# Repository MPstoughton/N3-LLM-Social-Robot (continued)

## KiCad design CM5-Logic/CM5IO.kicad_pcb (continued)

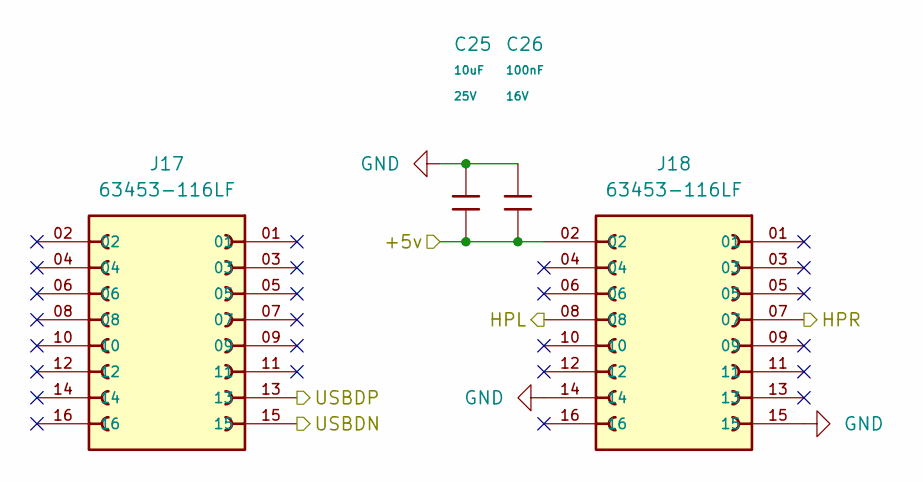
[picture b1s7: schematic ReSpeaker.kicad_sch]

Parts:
C25: 10uF; C_0805; Voltage Rated 25V; Tolerance ±10%; Part CL21A106KAYNNNE; LCSC C15850
C26: 100nF; C_0402; Voltage Rated 16V; Tolerance ±10%; Part CL05B104KO5NNNC; LCSC C1525
J17, J18: 63453-116LF; AMPHENOL_63453-116LF

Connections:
/+5v: C25.2, C26.2, J18.02; also elsewhere on the board
/HPL: J18.08; also elsewhere on the board
/HPR: J18.07; also elsewhere on the board
/USB2-D_N: J17.15; also elsewhere on the board
/USB2-D_P: J17.13; also elsewhere on the board
GND: C25.1, C26.1, J18.14, J18.15; also elsewhere on the board

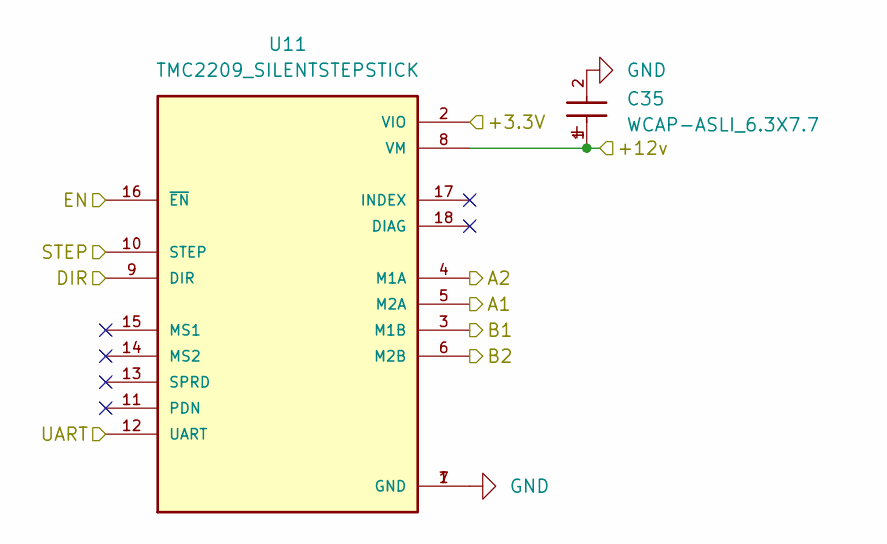
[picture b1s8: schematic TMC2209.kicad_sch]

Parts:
C35: WCAP-ASLI_6.3X7.7; WCAP-ASLI_6.3X7.7_DXL_
U11: TMC2209_SILENTSTEPSTICK; MODULE_TMC2209_SILENTSTEPSTICK; PARTREV 1.20

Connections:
/+3.3v_ESP32: U11.2 (VIO); also elsewhere on the board
/+12v: C35.1, U11.8 (VM); also elsewhere on the board
/TMC2209/A1: U11.5 (M2A); also elsewhere on the board
/TMC2209/A2: U11.4 (M1A); also elsewhere on the board
/TMC2209/B1: U11.3 (M1B); also elsewhere on the board
/TMC2209/B2: U11.6 (M2B); also elsewhere on the board
/n_Dir: U11.9 (DIR); also elsewhere on the board
/n_EN: U11.16 (~EN); also elsewhere on the board
/n_Step: U11.10 (STEP); also elsewhere on the board
/n_UART: U11.12 (UART); also elsewhere on the board
GND: C35.2, U11.1 (GND), U11.7 (GND); also elsewhere on the board

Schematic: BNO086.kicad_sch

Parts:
J13, J14: 6130XX11821_61300811821; 61300811821

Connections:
/+3.3v_ESP32: J13.4, J14.2; also elsewhere on the board
/BNO086/CS: J14.6
/BNO086/SCK: J14.3
/BNO086/SI: J14.5
/BNO086/SO: J14.4
/BNO086/WAK: J14.7
/n_INT: J13.8; also elsewhere on the board
/n_RST: J13.7; also elsewhere on the board
/n_SenseSCL: J13.6; also elsewhere on the board
/n_SenseSDA: J13.5; also elsewhere on the board
GND: J13.1, J13.2, J13.3, J14.1; also elsewhere on the board

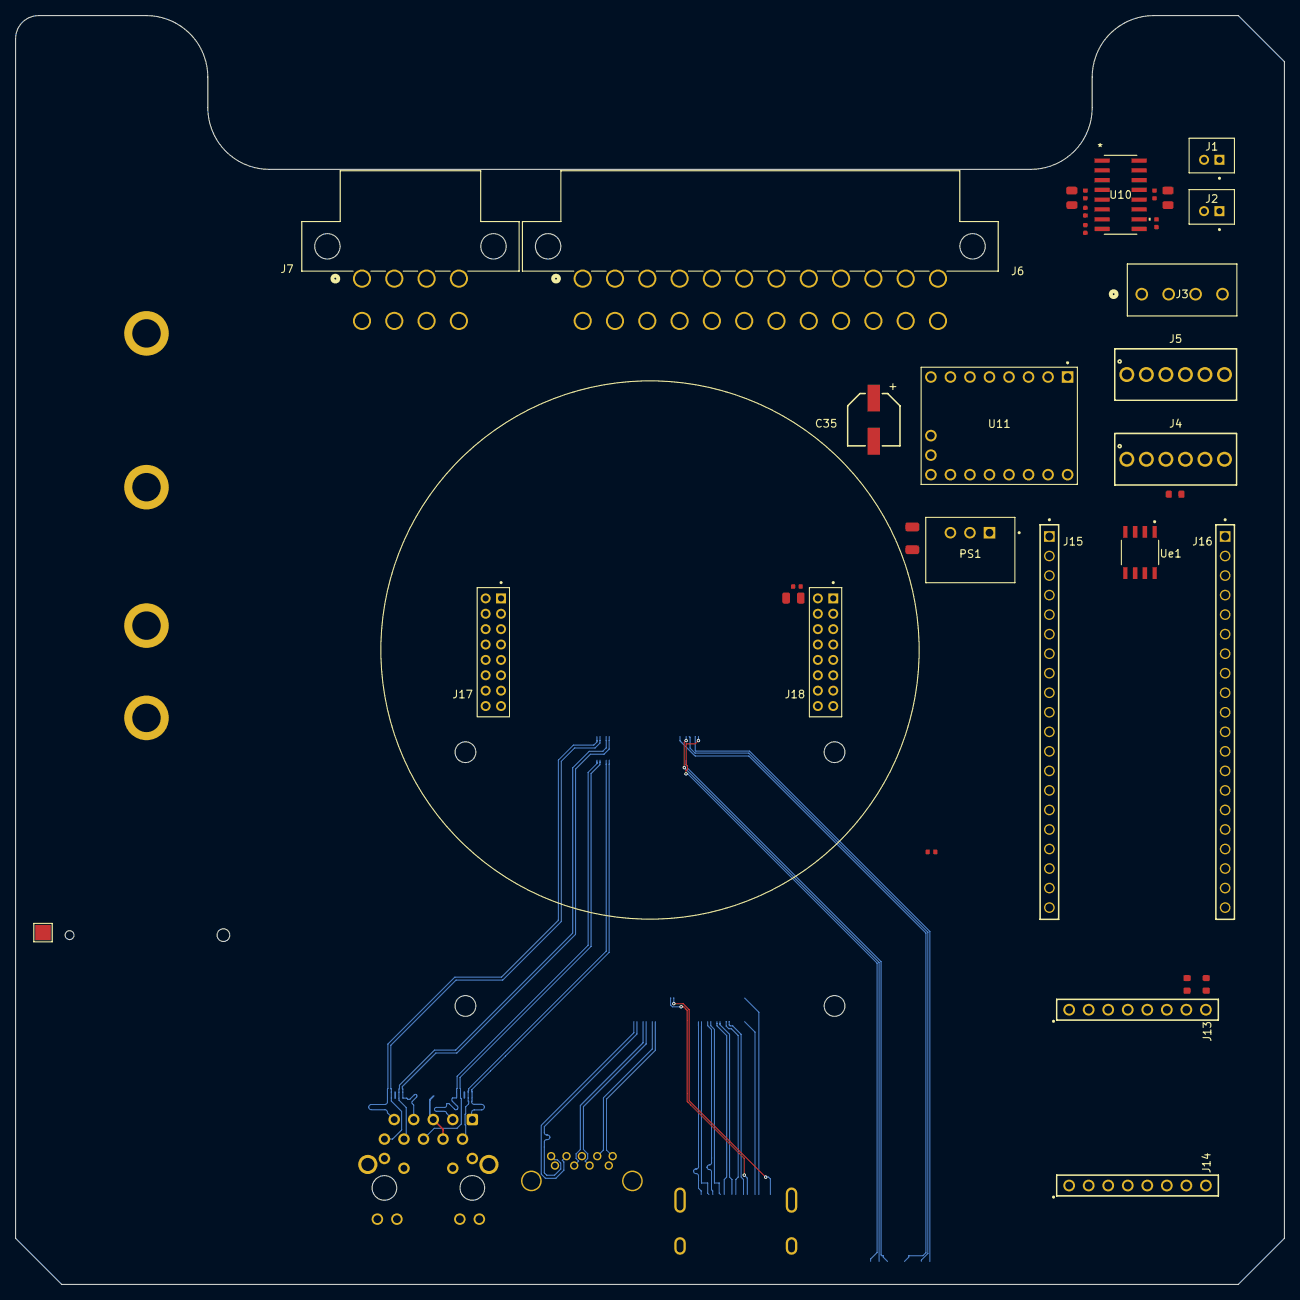
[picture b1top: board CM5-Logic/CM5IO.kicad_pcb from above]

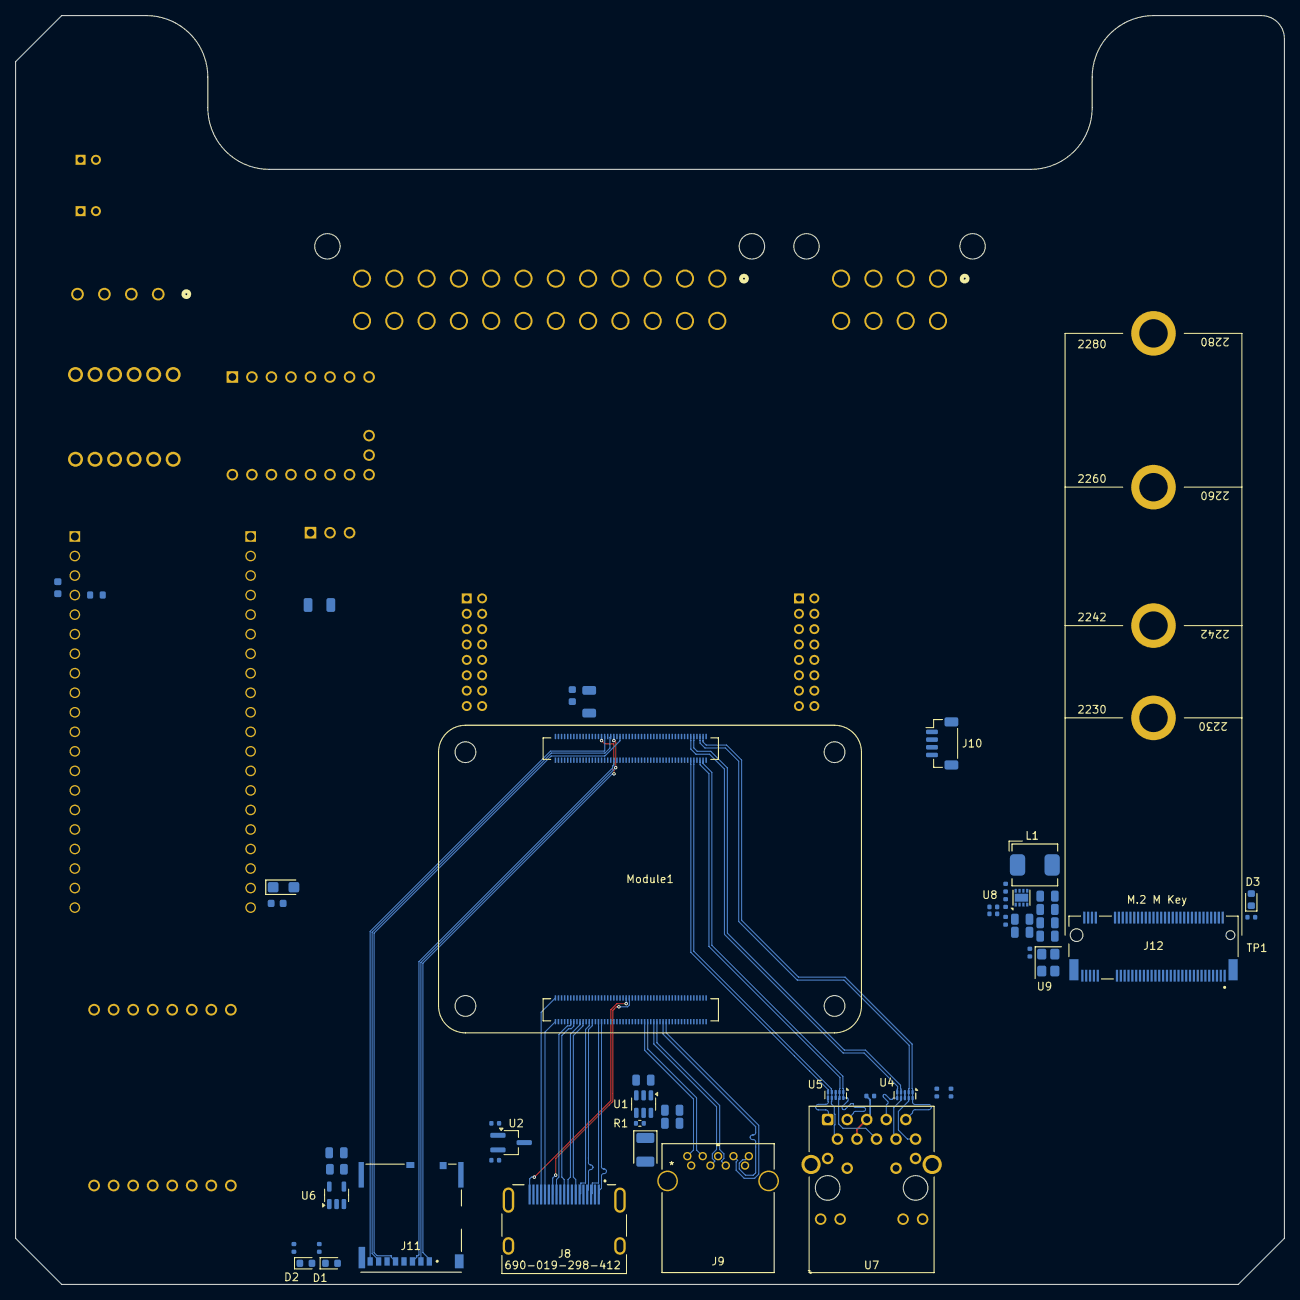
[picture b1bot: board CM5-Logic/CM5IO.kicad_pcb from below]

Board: 4 copper layers, 165.0 x 165.0 mm, 85 parts (52 on the bottom side), 107 nets.

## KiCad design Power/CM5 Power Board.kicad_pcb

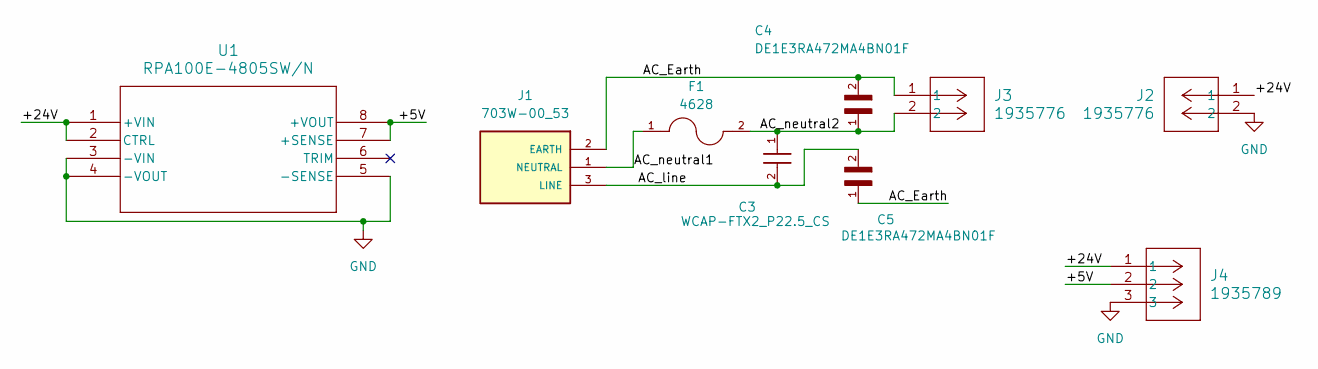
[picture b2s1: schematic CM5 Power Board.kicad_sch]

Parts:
C3: WCAP-FTX2_P22.5_CS; WCAP-FTX2_P22.5L26W6H12_CS
C4, C5: DE1E3RA472MA4BN01F; CAP_DE1E3RA472MA4BN01F
F1: 4628; FUSE_4628
J1: 703W-00_53; QUALTEK_703W-00_53
J2, J3: 1935776; CONN_1935776_PXC
J4: 1935789; CONN_1935789_PXC
U1: RPA100E-4805SW/N; RPA100E-W_RCP

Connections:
/+5V: J4.2, U1.7 (+SENSE), U1.8 (+VOUT)
/+24V: J2.1, J4.1, U1.1 (+VIN), U1.2 (CTRL)
/AC_Earth: C4.2, C5.1, J1.2 (EARTH), J3.1
/AC_line: C3.2, C5.2, J1.3 (LINE)
/AC_neutral1: F1.1, J1.1 (NEUTRAL)
/AC_neutral2: C3.1, C4.1, F1.2, J3.2
GND: J2.2, J4.3, U1.3 (-VIN), U1.4 (-VOUT), U1.5 (-SENSE)

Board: 2 copper layers, 9 parts (0 on the bottom side), 7 nets, no tracks yet.

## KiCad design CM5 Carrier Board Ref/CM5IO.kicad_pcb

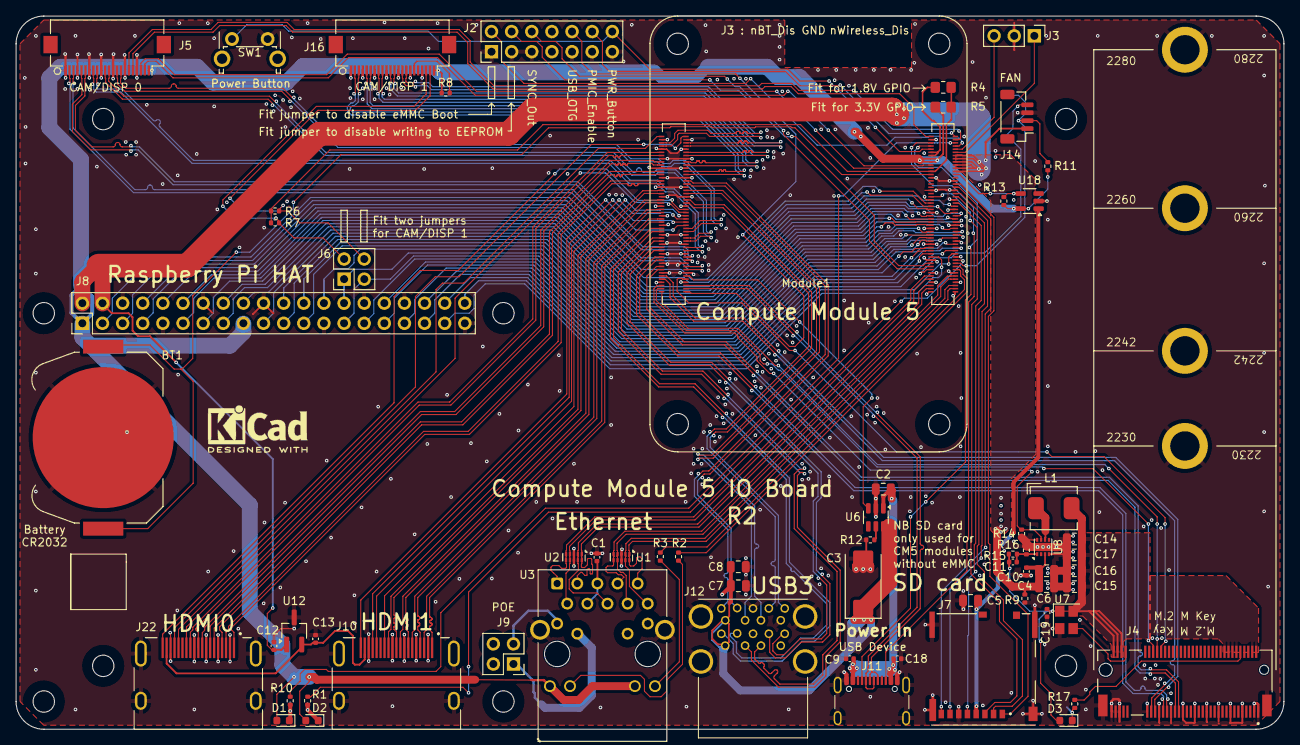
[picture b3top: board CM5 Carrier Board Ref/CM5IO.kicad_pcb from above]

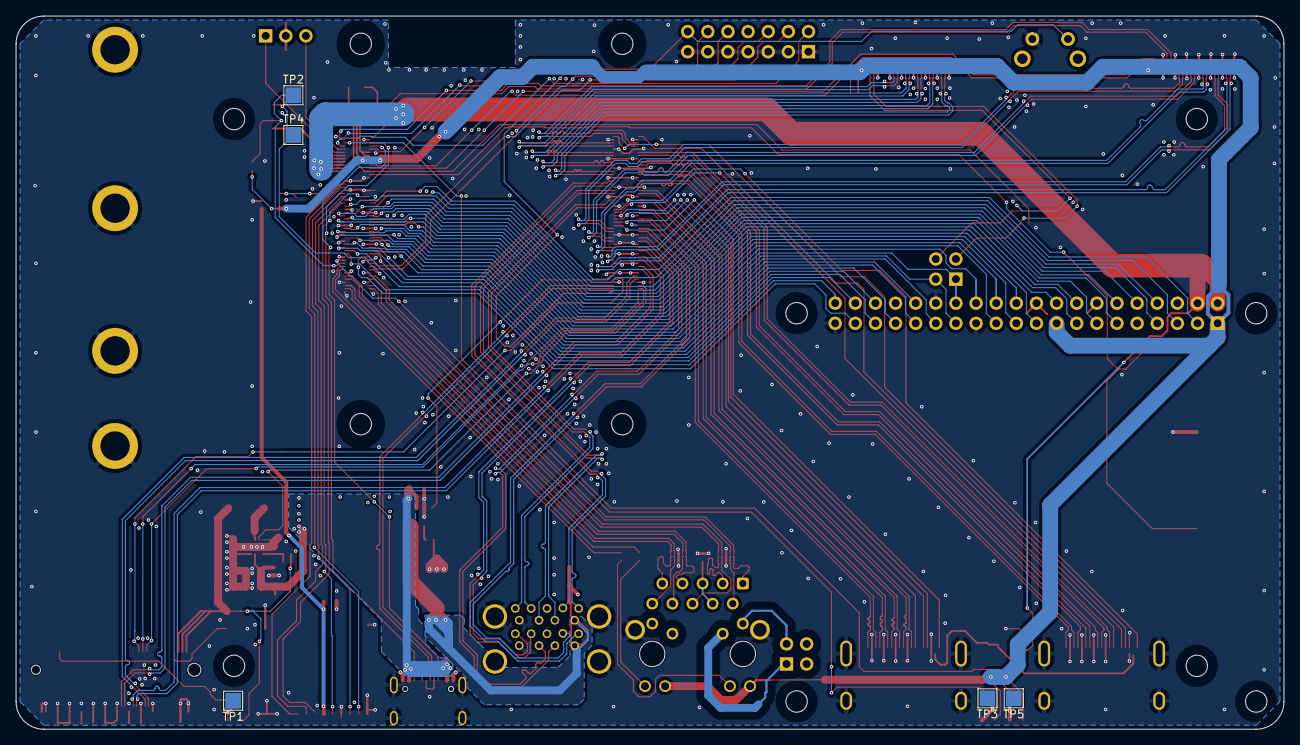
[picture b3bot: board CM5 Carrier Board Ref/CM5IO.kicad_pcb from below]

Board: 4 copper layers, 160.0 x 90.0 mm, 78 parts (5 on the bottom side), 160 nets.

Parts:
BT1: Battery_Cell; BatteryHolder_Keystone_3034_1x20mm
C1, C9, C10, C12, C13, C18, C19: 100n; C_0402_1005Metric
C2, C4, C5, C6, C7, C8, C14, C15, C16, C17: 10u; C_0805_2012Metric
C3: 100uF; CP_EIA-7343-31_Kemet-D
C11: 4.7nF; C_0402_1005Metric
D1: LED Red; LED_0603_1608Metric
D2, D3: LED Green; LED_0603_1608Metric
H1, H2, H3, H4, H5, H6, H7, H8: MountingHole; MountingHole_2.7mm_M2.5_DIN965
J2: Conn_02x07_Odd_Even; PinHeader_2x07_P2.54mm_Vertical
J3: Conn_01x03; PinHeader_1x03_P2.54mm_Vertical
J4: Bus_M.2_Socket_M; M.2 M Key socket
J5, J16: Conn_01x22_Female; Hirose_FH12-22S-0.5SH_1x22-1MP_P0.50mm_Horizontal
J6, J9: THD-02-R; PinHeader_2x02_P2.54mm_Vertical
J7: Micro_SD_Card_Det; SDCARD_MOLEX_503398-1892
J8: THD-20-R; PinHeader_2x20_P2.54mm_Vertical
J10, J22: 690-019-298-412; EDAC 690-019-298-412
J11: USB_C_Receptacle_USB2.0; USB_C_Receptacle_GCT_USB4105-xx-A_16P_TopMnt_Horizontal
J12: USB3_A; MTCONN_UBAF30-D2011
J14: JST_SHBM04B-SRSS-TB; JST_SH_BM04B-SRSS-TB_1x04-1MP_P1.00mm_Vertical
L1: 2.2uH; L_Bourns_SRP5030CC
Module1: ComputeModule5-CM5; Raspberry-Pi-5-Compute-Module
R1, R10, R17: 1k; R_0402_1005Metric
R2, R3: 470R; R_0402_1005Metric
R4: nf; R_0805_2012Metric_Pad1.20x1.40mm_HandSolder
R5: 0R; R_0805_2012Metric_Pad1.20x1.40mm_HandSolder
R6, R7, R8, R9, R16: 2.2K 1%; R_0402_1005Metric
R11, R13, R15: 10K 1%; R_0402_1005Metric
R12: 15K 1%; R_0402_1005Metric
R14: 100K 1%; R_0402_1005Metric
SW1: Right angle Tact button; SW_Tactile_SPST_Angled_PTS645Vx58-2LFS
TP1, TP2, TP3, TP4, TP5: TestPoint; TestPoint_Pad_2.0x2.0mm
U1, U2: TPD4EUSB30; USON-10_2.5x1.0mm_P0.5mm
U3: MagJack-A70-112-331N126; TRJG0926HENL
U6: AP22653W6; SOT-23-6
U7: ASEK-32.768KHZ-L-R-T; Crystal_SMD_3225-4Pin_3.2x2.5mm
U8: AP3441SHE-7B; DFN-8-1EP_2x2mm_P0.5mm_EP1.05x1.75mm
U12: RT9742SNGV; TSOT-23_HandSoldering
U18: RT9742GGJ5; SOT-23-5

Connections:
/+3.3v: D1.2 (A), D2.2 (A), J5.22, J8.1, J8.17, J16.22, Module1.84 (+3.3v_(Output)), Module1.86 (+3.3v_(Output)), R5.1, R8.1, R11.1, R13.1, U3.15 (LEDY_A), U3.17 (LEDG_A), U18.5 (IN)
/+5v: C2.1, C4.1, C6.1, C9.1, C10.1, C12.1, C18.1, J8.2, J8.4, J11.A4 (VBUS), J11.A9 (VBUS), J11.B4 (VBUS), J11.B9 (VBUS), J14.1, Module1.77 (+5v_(Input)), Module1.79 (+5v_(Input)), Module1.81 (+5v_(Input)), Module1.83 (+5v_(Input)), Module1.85 (+5v_(Input)), Module1.87 (+5v_(Input)), R9.1, U6.1 (IN), U8.3 (VIN), U12.1 (IN)
/CC1: J11.A5 (CC1), Module1.94 (CC1)
/CC2: J11.B5 (CC2), Module1.96 (CC2)
/CM5_GPIO ( Ethernet, GPIO, SDCARD)/+1.8v: Module1.88 (+1.8v_(Output)), Module1.90 (+1.8v_(Output)), R4.1
/CM5_GPIO ( Ethernet, GPIO, SDCARD)/BT_nDis: J3.3, Module1.91 (BT_nDisable)
/CM5_GPIO ( Ethernet, GPIO, SDCARD)/CAM_GPIO0: J5.17, Module1.97 (CAM_GPIO0)
/CM5_GPIO ( Ethernet, GPIO, SDCARD)/CAM_GPIO1: J5.18, Module1.100 (CAM_GPIO1)
/CM5_GPIO ( Ethernet, GPIO, SDCARD)/EEPROM_nWP: J2.4, Module1.20 (EEPROM_nWP)
/CM5_GPIO ( Ethernet, GPIO, SDCARD)/ETH_LEDG: Module1.17 (Ethernet_nLED2(3.3v)), R2.2
/CM5_GPIO ( Ethernet, GPIO, SDCARD)/ETH_LEDY: Module1.15 (Ethernet_nLED3(3.3v)), R3.2
/CM5_GPIO ( Ethernet, GPIO, SDCARD)/GPIO2: J8.3, Module1.58 (GPIO2)
/CM5_GPIO ( Ethernet, GPIO, SDCARD)/GPIO3: J8.5, Module1.56 (GPIO3)
/CM5_GPIO ( Ethernet, GPIO, SDCARD)/GPIO4: J8.7, Module1.54 (GPIO4)
/CM5_GPIO ( Ethernet, GPIO, SDCARD)/GPIO5: J8.29, Module1.34 (GPIO5)
/CM5_GPIO ( Ethernet, GPIO, SDCARD)/GPIO6: J8.31, Module1.30 (GPIO6)
/CM5_GPIO ( Ethernet, GPIO, SDCARD)/GPIO7: J8.26, Module1.37 (GPIO7)
/CM5_GPIO ( Ethernet, GPIO, SDCARD)/GPIO8: J8.24, Module1.39 (GPIO8)
/CM5_GPIO ( Ethernet, GPIO, SDCARD)/GPIO9: J8.21, Module1.40 (GPIO9)
/CM5_GPIO ( Ethernet, GPIO, SDCARD)/GPIO10: J8.19, Module1.44 (GPIO10)
/CM5_GPIO ( Ethernet, GPIO, SDCARD)/GPIO11: J8.23, Module1.38 (GPIO11)
/CM5_GPIO ( Ethernet, GPIO, SDCARD)/GPIO12: J8.32, Module1.31 (GPIO12)
/CM5_GPIO ( Ethernet, GPIO, SDCARD)/GPIO13: J8.33, Module1.28 (GPIO13)
/CM5_GPIO ( Ethernet, GPIO, SDCARD)/GPIO14: J8.8, Module1.55 (GPIO14)
/CM5_GPIO ( Ethernet, GPIO, SDCARD)/GPIO15: J8.10, Module1.51 (GPIO15)
/CM5_GPIO ( Ethernet, GPIO, SDCARD)/GPIO16: J8.36, Module1.29 (GPIO16)
/CM5_GPIO ( Ethernet, GPIO, SDCARD)/GPIO17: J8.11, Module1.50 (GPIO17)
/CM5_GPIO ( Ethernet, GPIO, SDCARD)/GPIO18: J8.12, Module1.49 (GPIO18)
/CM5_GPIO ( Ethernet, GPIO, SDCARD)/GPIO19: J8.35, Module1.26 (GPIO19)
/CM5_GPIO ( Ethernet, GPIO, SDCARD)/GPIO20: J8.38, Module1.27 (GPIO20)
/CM5_GPIO ( Ethernet, GPIO, SDCARD)/GPIO21: J8.40, Module1.25 (GPIO21)
/CM5_GPIO ( Ethernet, GPIO, SDCARD)/GPIO22: J8.15, Module1.46 (GPIO22)
/CM5_GPIO ( Ethernet, GPIO, SDCARD)/GPIO23: J8.16, Module1.47 (GPIO23)
/CM5_GPIO ( Ethernet, GPIO, SDCARD)/GPIO24: J8.18, Module1.45 (GPIO24)
/CM5_GPIO ( Ethernet, GPIO, SDCARD)/GPIO25: J8.22, Module1.41 (GPIO25)
/CM5_GPIO ( Ethernet, GPIO, SDCARD)/GPIO26: J8.37, Module1.24 (GPIO26)
/CM5_GPIO ( Ethernet, GPIO, SDCARD)/GPIO27: J8.13, Module1.48 (GPIO27)
/CM5_GPIO ( Ethernet, GPIO, SDCARD)/GPIO_VREF: Module1.78 (GPIO_VREF(1.8v/3.3v_Input)), R4.2, R5.2, R6.1, R7.1
/CM5_GPIO ( Ethernet, GPIO, SDCARD)/ID_SC: J6.1, J8.28, Module1.35 (ID_SC)
/CM5_GPIO ( Ethernet, GPIO, SDCARD)/ID_SD: J6.3, J8.27, Module1.36 (ID_SD)
/CM5_GPIO ( Ethernet, GPIO, SDCARD)/PMIC_ENABLE: J2.12, Module1.99 (PMIC_ENABLE)
/CM5_GPIO ( Ethernet, GPIO, SDCARD)/PWM: J14.2, Module1.19 (FAN_PWM), R11.2, TP2.1
/CM5_GPIO ( Ethernet, GPIO, SDCARD)/PWR_BUT: J2.14, Module1.92 (PWR_BUT), SW1.1
/CM5_GPIO ( Ethernet, GPIO, SDCARD)/SD_CLK: J7.5 (CLK), Module1.57 (SD_CLK)
/CM5_GPIO ( Ethernet, GPIO, SDCARD)/SD_CMD: J7.3 (CMD), Module1.62 (SD_CMD)
/CM5_GPIO ( Ethernet, GPIO, SDCARD)/SD_DAT0: J7.7 (DAT0), Module1.63 (SD_DAT0)
/CM5_GPIO ( Ethernet, GPIO, SDCARD)/SD_DAT1: J7.8 (DAT1), Module1.67 (SD_DAT1)
/CM5_GPIO ( Ethernet, GPIO, SDCARD)/SD_DAT2: J7.1 (DAT2), Module1.69 (SD_DAT2)
/CM5_GPIO ( Ethernet, GPIO, SDCARD)/SD_DAT3: J7.2 (DAT3/CD), Module1.61 (SD_DAT3)
/CM5_GPIO ( Ethernet, GPIO, SDCARD)/SD_PWR: C5.1, J7.4 (VDD), U18.1 (OUT)
/CM5_GPIO ( Ethernet, GPIO, SDCARD)/SD_PWR_ON: Module1.75 (SD_PWR_ON), R13.2, U18.4 (EN)
/CM5_GPIO ( Ethernet, GPIO, SDCARD)/SYNC_OUT: J2.6, Module1.18 (Ethernet_SYNC_OUT(3.3v))
/CM5_GPIO ( Ethernet, GPIO, SDCARD)/TACHO: J14.4, Module1.16 (FAN_TACHO), TP4.1
/CM5_GPIO ( Ethernet, GPIO, SDCARD)/TR0_TAP: J9.3, U3.11 (VC1)
/CM5_GPIO ( Ethernet, GPIO, SDCARD)/TR1_TAP: J9.1, U3.12 (VC2)
/CM5_GPIO ( Ethernet, GPIO, SDCARD)/TR2_TAP: J9.2, U3.13 (VC3)
/CM5_GPIO ( Ethernet, GPIO, SDCARD)/TR3_TAP: J9.4, U3.14 (VC4)
/CM5_GPIO ( Ethernet, GPIO, SDCARD)/TRD0_N: Module1.10 (Ethernet_Pair0_N), U2.4 (D2+), U2.7, U3.2 (TRD0-)
/CM5_GPIO ( Ethernet, GPIO, SDCARD)/TRD0_P: Module1.12 (Ethernet_Pair0_P), U2.5 (D2-), U2.6, U3.1 (TRD0+)
/CM5_GPIO ( Ethernet, GPIO, SDCARD)/TRD1_N: Module1.6 (Ethernet_Pair1_N), U2.2 (D1-), U2.9, U3.6 (TRD1-)
/CM5_GPIO ( Ethernet, GPIO, SDCARD)/TRD1_P: Module1.4 (Ethernet_Pair1_P), U2.1 (D1+), U2.10, U3.3 (TRD1+)
/CM5_GPIO ( Ethernet, GPIO, SDCARD)/TRD2_N: Module1.9 (Ethernet_Pair2_N), U1.4 (D2+), U1.7, U3.8 (TRD2-)
/CM5_GPIO ( Ethernet, GPIO, SDCARD)/TRD2_P: Module1.11 (Ethernet_Pair2_P), U1.5 (D2-), U1.6, U3.7 (TRD2+)
/CM5_GPIO ( Ethernet, GPIO, SDCARD)/TRD3_N: Module1.5 (Ethernet_Pair3_N), U1.2 (D1-), U1.9, U3.10 (TRD3-)
/CM5_GPIO ( Ethernet, GPIO, SDCARD)/TRD3_P: Module1.3 (Ethernet_Pair3_P), U1.1 (D1+), U1.10, U3.9 (TRD3+)
/CM5_GPIO ( Ethernet, GPIO, SDCARD)/USBOTG: J2.10, Module1.101 (USB_OTG_ID)
/CM5_GPIO ( Ethernet, GPIO, SDCARD)/VBAT: BT1.1 (+), Module1.76 (VBAT)
/CM5_GPIO ( Ethernet, GPIO, SDCARD)/WL_nDis: J3.1, Module1.89 (WiFi_nDisable)
/CM5_GPIO ( Ethernet, GPIO, SDCARD)/nPWR_LED: Module1.95 (LED_nPWR), R10.2
/CM5_GPIO ( Ethernet, GPIO, SDCARD)/nRPIBOOT: J2.2, Module1.93 (nRPIBOOT)
/CM5_HighSpeed/DPHY0_C_N: J5.8, Module1.127 (MIPI0_C_N)
/CM5_HighSpeed/DPHY0_C_P: J5.9, Module1.129 (MIPI0_C_P)
/CM5_HighSpeed/DPHY0_D0_N: J5.2, Module1.115 (MIPI0_D0_N)
/CM5_HighSpeed/DPHY0_D0_P: J5.3, Module1.117 (MIPI0_D0_P)
/CM5_HighSpeed/DPHY0_D1_N: J5.5, Module1.121 (MIPI0_D1_N)
/CM5_HighSpeed/DPHY0_D1_P: J5.6, Module1.123 (MIPI0_D1_P)
/CM5_HighSpeed/DPHY0_D2_N: J5.11, Module1.133 (MIPI0_D2_N)
/CM5_HighSpeed/DPHY0_D2_P: J5.12, Module1.135 (MIPI0_D2_P)
/CM5_HighSpeed/DPHY0_D3_N: J5.14, Module1.139 (MIPI0_D3_N)
/CM5_HighSpeed/DPHY0_D3_P: J5.15, Module1.141 (MIPI0_D3_P)
/CM5_HighSpeed/DPHY1_C_N: J16.8, Module1.187 (MIPI1_C_N)
/CM5_HighSpeed/DPHY1_C_P: J16.9, Module1.189 (MIPI1_C_P)
/CM5_HighSpeed/DPHY1_D0_N: J16.2, Module1.175 (MIPI1_D0_N)
/CM5_HighSpeed/DPHY1_D0_P: J16.3, Module1.177 (MIPI1_D0_P)
/CM5_HighSpeed/DPHY1_D1_N: J16.5, Module1.181 (MIPI1_D1_N)
/CM5_HighSpeed/DPHY1_D1_P: J16.6, Module1.183 (MIPI1_D1_P)
/CM5_HighSpeed/DPHY1_D2_N: J16.11, Module1.193 (MIPI1_D2_N)
/CM5_HighSpeed/DPHY1_D2_P: J16.12, Module1.195 (MIPI1_D2_P)
/CM5_HighSpeed/DPHY1_D3_N: J16.14, Module1.194 (MIPI1_D3_N)
/CM5_HighSpeed/DPHY1_D3_P: J16.15, Module1.196 (MIPI1_D3_P)
/CM5_HighSpeed/HDMI0_CEC: J22.13 (CEC), Module1.151 (HDMI0_CEC)
/CM5_HighSpeed/HDMI0_CK_N: J22.12 (CK-), Module1.190 (HDMI0_CLK_N)
/CM5_HighSpeed/HDMI0_CK_P: J22.10 (CK+), Module1.188 (HDMI0_CLK_P)
/CM5_HighSpeed/HDMI0_D0_N: J22.9 (D0-), Module1.184 (HDMI0_TX0_N)
/CM5_HighSpeed/HDMI0_D0_P: J22.7 (D0+), Module1.182 (HDMI0_TX0_P)
/CM5_HighSpeed/HDMI0_D1_N: J22.6 (D1-), Module1.178 (HDMI0_TX1_N)
/CM5_HighSpeed/HDMI0_D1_P: J22.4 (D1+), Module1.176 (HDMI0_TX1_P)
/CM5_HighSpeed/HDMI0_D2_N: J22.3 (D2-), Module1.172 (HDMI0_TX2_N)
/CM5_HighSpeed/HDMI0_D2_P: J22.1 (D2+), Module1.170 (HDMI0_TX2_P)
/CM5_HighSpeed/HDMI0_HOTPLUG: J22.19 (HPD/HEAC-), Module1.153 (HDMI0_HOTPLUG)
/CM5_HighSpeed/HDMI0_SCL: J22.15 (SCL), Module1.200 (HDMI0_SCL)
/CM5_HighSpeed/HDMI0_SDA: J22.16 (SDA), Module1.199 (HDMI0_SDA)
/CM5_HighSpeed/HDMI1_CEC: J10.13 (CEC), Module1.149 (HDMI1_CEC)
/CM5_HighSpeed/HDMI1_CK_N: J10.12 (CK-), Module1.166 (HDMI1_CLK_N)
/CM5_HighSpeed/HDMI1_CK_P: J10.10 (CK+), Module1.164 (HDMI1_CLK_P)
/CM5_HighSpeed/HDMI1_D0_N: J10.9 (D0-), Module1.160 (HDMI1_TX0_N)
/CM5_HighSpeed/HDMI1_D0_P: J10.7 (D0+), Module1.158 (HDMI1_TX0_P)
/CM5_HighSpeed/HDMI1_D1_N: J10.6 (D1-), Module1.154 (HDMI1_TX1_N)
/CM5_HighSpeed/HDMI1_D1_P: J10.4 (D1+), Module1.152 (HDMI1_TX1_P)
/CM5_HighSpeed/HDMI1_D2_N: J10.3 (D2-), Module1.148 (HDMI1_TX2_N)
/CM5_HighSpeed/HDMI1_D2_P: J10.1 (D2+), Module1.146 (HDMI1_TX2_P)
/CM5_HighSpeed/HDMI1_HOTPLUG: J10.19 (HPD/HEAC-), Module1.143 (HDMI1_HOTPLUG)
/CM5_HighSpeed/HDMI1_SCL: J10.15 (SCL), Module1.147 (HDMI1_SCL)
/CM5_HighSpeed/HDMI1_SDA: J10.16 (SDA), Module1.145 (HDMI1_SDA)
/CM5_HighSpeed/HDMI_5v: C13.1, J10.18 (+5V), J22.18 (+5V), U12.2 (OUT)
/CM5_HighSpeed/PCIE_CLK_N: J4.53 (REFCLKn), Module1.112 (PCIe_CLK_N)
/CM5_HighSpeed/PCIE_CLK_P: J4.55 (REFCLKp), Module1.110 (PCIe_CLK_P)
/CM5_HighSpeed/PCIE_PWR_EN: Module1.106 (PCIE_PWR_EN), R14.1, U8.7 (EN)
/CM5_HighSpeed/PCIE_RX_N: J4.43 (PETp0), Module1.118 (PCIe_RX_N)
/CM5_HighSpeed/PCIE_RX_P: J4.41 (PETn0), Module1.116 (PCIe_RX_P)
/CM5_HighSpeed/PCIE_TX_N: J4.49 (PERp0), Module1.124 (PCIe_TX_N)
/CM5_HighSpeed/PCIE_TX_P: J4.47 (PERn0), Module1.122 (PCIe_TX_P)
/CM5_HighSpeed/PCIE_nCLKREQ: J4.52 (~CLKREQ), Module1.102 (PCIe_nCLKREQ)
/CM5_HighSpeed/PCIE_nRST: J4.50 (~PERST), Module1.109 (PCIe_nRST)
/CM5_HighSpeed/PCIE_nWAKE: J4.54 (~PEWAKE), Module1.104 (PCIE_nWAKE)
/CM5_HighSpeed/SCL0: J5.20, Module1.80 (SCL0)
/CM5_HighSpeed/SCL1: J6.2, J16.20, R7.2
/CM5_HighSpeed/SDA0: J5.21, Module1.82 (SDA0)
/CM5_HighSpeed/SDA1: J6.4, J16.21, R6.2
/CM5_HighSpeed/USB3-0-D_N: J12.A2 (D-), Module1.136 (USB3-0-D_N)
/CM5_HighSpeed/USB3-0-D_P: J12.A3 (D+), Module1.134 (USB3-0-D_P)
/CM5_HighSpeed/USB3-0-RX_N: J12.A6 (SSRX+), Module1.128 (USB3-0-RX_N)
/CM5_HighSpeed/USB3-0-RX_P: J12.A5 (SSRX-), Module1.130 (USB3-0-RX_P)
/CM5_HighSpeed/USB3-0-TX_N: J12.A9 (SSTX+), Module1.140 (USB3-0-TX_N)
/CM5_HighSpeed/USB3-0-TX_P: J12.A8 (SSTX-), Module1.142 (USB3-0-TX_P)
/CM5_HighSpeed/USB3-1-D_N: J12.B2 (D-), Module1.165 (USB3-1-D_N)
/CM5_HighSpeed/USB3-1-D_P: J12.B3 (D+), Module1.163 (USB3-1-D_P)
/CM5_HighSpeed/USB3-1-RX_N: J12.B6 (SSRX+), Module1.157 (USB3-1-RX_N)
/CM5_HighSpeed/USB3-1-RX_P: J12.B5 (SSRX-), Module1.159 (USB3-1-RX_P)
/CM5_HighSpeed/USB3-1-TX_N: J12.B9 (SSTX+), Module1.169 (USB3-1-TX_N)
/CM5_HighSpeed/USB3-1-TX_P: J12.B8 (SSTX-), Module1.171 (USB3-1-TX_P)
/CM5_HighSpeed/VBUS: C3.1, C7.1, C8.1, J12.A1 (VBUS), J12.B1 (VBUS), U6.6 (OUT)
/CM5_HighSpeed/VBUS_EN: Module1.111 (VBUS_EN), U6.3 (EN)
/PCIe-M2/FB: C11.2, R15.2, R16.1, U8.1 (FB)
/PCIe-M2/M2_3v3: C11.1, C14.1, C15.1, C16.1, C17.1, C19.1, D3.2 (A), J4.2 (3.3V), J4.4 (3.3V), J4.12 (3.3V), J4.14 (3.3V), J4.16 (3.3V), J4.18 (3.3V), J4.70 (3.3V), J4.72 (3.3V), J4.74 (3.3V), L1.2, R15.1, U7.1 (EN), U7.4 (VDD)
/USB2_N: J11.A7 (D-), J11.B7 (D-), Module1.103 (USB2_N)
/USB2_P: J11.A6 (D+), J11.B6 (D+), Module1.105 (USB2_P)
GND: BT1.2 (-), C1.2, C2.2, C3.2, C4.2, C5.2, C6.2, C7.2, C8.2, C9.2, C10.2, C12.2, C13.2, C14.2, C15.2, C16.2, C17.2, C18.2, C19.2, J2.1, J2.3, J2.5, J2.7, J2.9, J2.11, J2.13, J3.2, J4.1 (GND), J4.3 (GND), J4.9 (GND), J4.15 (GND), J4.21 (GND), J4.27 (GND), J4.33 (GND), J4.39 (GND), J4.45 (GND), J4.51 (GND), J4.57 (GND), J4.71 (GND), J4.73 (GND), J4.75 (GND), J4.M1 (GND2230), J4.M2 (GND2242), J4.M3 (GND2260), J4.M4 (GND2280), J4.S1, J4.S2, J5.1, J5.4, J5.7, J5.10, J5.13, J5.16, J5.19, J7.6 (VSS), J7.11 (SHIELD), J8.6, J8.9, J8.14, J8.20, J8.25, J8.30, J8.34, J8.39, J10.2 (D2S), J10.5 (D1S), J10.8 (D0S), J10.11 (CKS), J10.17 (GND), J10.SH1 (SH), J10.SH2 (SH), J10.SH3 (SH), J10.SH4 (SH), J11.A1 (GND), J11.A12 (GND), J11.B1 (GND), J11.B12 (GND), J11.S1 (SHIELD), J12.10 (SHIELD), J12.A4 (GND), J12.A7 (DRAIN), J12.B4 (GND), J12.B7 (DRAIN), J14.3, J16.1, J16.4, J16.7, J16.10, J16.13, J16.16, J16.19, J22.2 (D2S), J22.5 (D1S), J22.8 (D0S), J22.11 (CKS), J22.17 (GND), J22.SH1 (SH), J22.SH2 (SH), J22.SH3 (SH), J22.SH4 (SH), Module1.1 (GND), Module1.2 (GND), Module1.7 (GND), Module1.8 (GND), Module1.13 (GND), Module1.14 (GND), Module1.22 (GND), Module1.23 (GND), Module1.32 (GND), Module1.33 (GND), Module1.42 (GND), Module1.43 (GND), Module1.52 (GND), Module1.53 (GND), Module1.59 (GND), Module1.60 (GND), Module1.65 (GND), Module1.66 (GND), Module1.71 (GND), Module1.74 (GND), Module1.98 (GND), Module1.107 (GND), Module1.108 (GND), Module1.113 (GND), Module1.114 (GND), Module1.119 (GND), Module1.120 (GND), Module1.125 (GND), Module1.126 (GND), Module1.131 (GND), Module1.132 (GND), Module1.137 (GND), Module1.138 (GND), Module1.144 (GND), Module1.150 (GND), Module1.155 (GND), Module1.156 (GND), Module1.161 (GND), Module1.162 (GND), Module1.167 (GND), Module1.168 (GND), Module1.173 (GND), Module1.174 (GND), Module1.179 (GND), Module1.180 (GND), Module1.185 (GND), Module1.186 (GND), Module1.191 (GND), Module1.192 (GND), Module1.197 (GND), Module1.198 (GND), R9.2, R12.2, R14.2, R16.2, SW1.2, U1.3 (GND), U1.8 (GND), U2.3 (GND), U2.8 (GND), U3.19 (SHIELD), U3.20 (SHIELD), U6.2 (GND), U7.2 (GND), U8.4 (PGND), U8.8 (SGND), U8.9 (PAD), U12.3 (GND), U18.2 (GND)
unnamed: C1.1, U3.4 (CT), U3.5 (CT)
unnamed: D1.1 (K), R10.1, TP5.1
unnamed: D2.1 (K), R1.1, TP3.1
unnamed: D3.1 (K), R17.1, TP1.1
unnamed: J4.10 (DAS/~DSS/~LED1), R17.2
unnamed: J4.68 (SUSCLK), U7.3 (Out)
unnamed: J16.17, R8.2
unnamed: Module1.21 (LED_nACT), R1.2
unnamed: R3.1, U3.18 (LEDG_K)
unnamed: R2.1, U3.16 (LEDY_K)
unnamed: R12.1, U6.5 (ILIM)
unnamed: L1.1, U8.6 (LX)

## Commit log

2025-06-12 Commit innitial board
2025-06-12 fix initial board commit
2025-06-12 deletes power and vestigial connectors
2025-06-12 retructure file
2025-06-16 adds base coil design
2025-06-18 adds TX coil PCB and 3D Ansys Maxwell FEA validation for V1
2025-06-18 adds TX coil half bridge to power board
2025-06-20 corrects power board for 400W max power production at 24v and 5v rail
2025-07-08 adds respeaker and reworks the amplifier
2025-07-09 adds power connector and works on the ESP32 outputs
2025-07-09 fixes a few label issues
2025-07-10 fixes all label issues and power input pins
2025-07-10 adds a base motor driver with UART integration for the ESP32-S3-DC1 base hub
2025-07-15 adds a 24Pin ATX PSU interface for power and cleans up the amplifier hierarchy
2025-07-16 adds the 8-PIN PSU EPS connction for higher available current on the CM5 Carrier board
2025-07-18 changes USB port, adds TMC2209 SilentStepStick footprint, redoes PCB Layout
2025-07-23 Finishes PCB Pad Layout, Updates LED Status Circuit to RPI Foundations newest version
2025-07-24 Routes and tunes ethernet/hdmi
2025-07-24 Routes and tunes most of the debug interface, upadtes 3D models
